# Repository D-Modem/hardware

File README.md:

# pico-serial

Open RP2040 boards for the D-Modem suite: serial adapters and phone-line
USB sticks.

pico-serial connects a phone or computer to vintage serial ports and to
real telephone lines. The phone or computer runs [D-Modem](https://github.com/D-Modem/D-Modem)
or [the D-Modem app](https://github.com/D-Modem/app). Each board has a bare
RP2040 with its own flash, crystal and regulator. The boards do not use a
Pico module.

| Board | What it is | Spec |
| --- | --- | --- |
| pico-serial | USB-C to DB25 RS-232. One female DB25 operates as a modem (DCE) or as a computer port (DTE). The board finds the mode automatically | [SPEC.md](SPEC.md) |
| pico-serial W | The same adapter with Bluetooth: BLE for iPhone and iPad, and classic Bluetooth serial for Android | [SPEC-W.md](SPEC-W.md) |
| pico-serial Line | A USB modem stick for a real telephone line, with a Si3056 DAA. The modem is D-Modem on the host | [SPEC-L.md](SPEC-L.md) |
| pico-serial WB | A wideband stick for bare copper pairs. It samples at 96 kHz for the V.wb mode of D-Modem | [SPEC-WB.md](SPEC-WB.md) |

Status: the specs are drafts. CI builds the firmware and runs its tests
on the host and in an RP2040 emulator. A script makes the board files for
KiCad 9. At this time, nothing has run on a real board.

## Quick start

```sh
cmake -S firmware -B firmware/build -G Ninja   # -DPS_BOARD=hood, w, line, wb or pico
ninja -C firmware/build                        # -> firmware/build/pico-serial-hood.uf2
```

The script `hardware/netlist/build_netlist.py` makes the board files.

## Documentation

The documentation is also a website, [d-modem.github.io/hardware](https://d-modem.github.io/hardware/). The website has reference pages that a script makes from the code.

- [docs/](docs/README.md): an index of all specs and guides
- [Firmware](firmware/README.md): how to build and flash, Bluetooth, tests
- [Control protocol](firmware/PROTOCOL.md): the USB vendor interface for host apps
- [Hardware](hardware/README.md): netlist, schematic, PCB, enclosures

## The D-Modem suite

| Repository | What it is |
| --- | --- |
| [D-Modem](https://github.com/D-Modem/D-Modem) | The open V.92 softmodem: dmodemd, libdmodem and the Asterisk, FreeSWITCH and ARI modules |
| [app](https://github.com/D-Modem/app) | The D-Modem app for Android and iOS: a dial-up modem on a SIP call |
| [hardware](https://github.com/D-Modem/hardware) | pico-serial: RP2040 serial adapters and phone-line USB sticks |
| [menu](https://github.com/D-Modem/menu) | modemmenu: the login and the menu that dial-up callers get to |
| [bbs](https://github.com/D-Modem/bbs) | A bulletin board for telnet, SSH, TN3270 and modem callers |
| [go3270](https://github.com/D-Modem/go3270) | A Go library for 3270 terminal servers, used by bbs |
| [brand](https://github.com/D-Modem/brand) | Logos, colours, type and the naming guide |

ISDN S0 stick (an ISDN basic rate S/T port for D-Modem, TE or NT): see [SPEC-S0.md](SPEC-S0.md).

FPGA line board (a study: ADSL, ISDN U or S0 through gateware and host software): see [SPEC-FX.md](SPEC-FX.md).

## Licence

Firmware: AGPL-3.0-only, or a commercial licence from the D-Modem Authors. Hardware: CERN-OHL-S-2.0, or a commercial licence from the D-Modem Authors. See [LICENSING.md](LICENSING.md). Contributions come with a contributor agreement ([CONTRIBUTING.md](CONTRIBUTING.md)).

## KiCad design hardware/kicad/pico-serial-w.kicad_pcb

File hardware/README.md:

<!-- SPDX-License-Identifier: CERN-OHL-S-2.0 -->
<!-- Copyright (C) 2026 D-Modem Authors -->
# pico-serial hardware

`netlist/build_netlist.py` defines all parts and all connections on the
board. The scripts make the netlist, the readable net list, the JLC parts
list, the schematic and the PCB from it. Thus, change the script, not the
outputs.

The script makes these boards:
- The **hood board** (the default). It fits in a standard DB25 hood.
- **pico-serial W** (`--variant w`, [SPEC-W.md](../SPEC-W.md)). It adds an
  RM2 Bluetooth module, and it is in a 3D-printed hood (`enclosure/`). Its
  files have a `-w` suffix. See [pico-serial W](#pico-serial-w-bluetooth).
- **pico-serial Line** (`--variant line`, [SPEC-L.md](../SPEC-L.md)). It is
  a different device on the same RP2040 core: a USB-C stick that connects to
  a telephone line, for D-Modem. Its files have a `-line` suffix. See
  [pico-serial Line](#pico-serial-line-phone-line-stick).

All files are for **KiCad 9**: KiCad 9 file formats and the KiCad 9.0
symbol and footprint libraries. KiCad 10 also opens them.

| File | What it is |
|---|---|
| `netlist/build_netlist.py` | The circuit: parts, nets, the checks |
| `netlist/pico-serial.net` | KiCad netlist (generated) |
| `netlist/NETLIST.md` | All nets and all parts, in a readable form (generated) |
| `netlist/bom-jlc.csv` | JLC assembly parts list with LCSC numbers (generated) |
| `kicad/build_schematic.py` | Draws the schematic from the netlist script |
| `kicad/pico-serial.kicad_sch` | KiCad schematic, one A2 sheet (generated) |
| `kicad/pico-serial.kicad_sym` | SP3238E and MAX3243E symbols. KiCad does not supply these symbols (generated) |
| `kicad/preview.svg` | Approximate drawing of the sheet for a quick examination (generated) |
| `kicad/build_pcb.py` | Makes the layout of the PCB and routes it: outline, rules, placement, planes |
| `kicad/pico-serial.kicad_pcb` | KiCad PCB, 4 layers (generated) |
| `kicad/pico-serial.kicad_dru` | Two DRC rules for this board (the DB25 cups and the USB-C shell at the edges) |
| `kicad/fab/` | Gerbers + drill (zip) and the JLC placement file (generated) |
| `kicad/render-top.png`, `render-bottom.png` | KiCad 3D renders, without part models (generated) |
| `netlist/pico-serial-w.net`, `NETLIST-w.md`, `bom-jlc-w.csv` | The same for pico-serial W (generated) |
| `kicad/pico-serial-w.*`, `preview-w.svg`, `render-w-*.png` | The schematic, PCB, rules and renders of pico-serial W |
| `kicad/lib/make_footprints.py` | Writes `lib/pico-serial.pretty/`: the RM2 (from the drawing in its datasheet), the M2 screw hole, the RJ11 and the telecom fuse |
| `netlist/*-line.*`, `kicad/pico-serial-line.*`, `kicad/render-line-*.png` | The netlist, BOM, schematic, PCB, rules and renders of pico-serial Line |
| `netlist/*-wb.*`, `kicad/pico-serial-wb.*`, `kicad/render-wb-*.png` | The netlist, BOM, schematic, PCB, rules and renders of pico-serial WB |
| `enclosure/stick.py`, `enclosure/out-line/` | The printed shell of the Line stick, its board outline and placement |
| `kicad/fp-lib-table` | Points KiCad to `lib/pico-serial.pretty` |

## Regenerate

```sh
python3 hardware/netlist/build_netlist.py       # checks + netlist, NETLIST.md, BOM
python3 hardware/kicad/build_schematic.py   # checks + schematic and preview
python3 hardware/kicad/build_pcb.py --kicad-fp kicad-footprints --route --fab   # PCB (see below)
```

For pico-serial W, add `--variant w` to each command.

The netlist and schematic scripts do not need KiCad or a network
connection. The schematic script uses the symbols in the cache
`kicad/lib/symbol-cache.sexp`.

To compare all pins with the libraries of KiCad, and to update the symbol
cache, give the scripts the checkouts of the KiCad 9.0 libraries:

```sh
git clone --depth 1 --branch 9.0.6 https://gitlab.com/kicad/libraries/kicad-symbols.git
git clone --depth 1 --branch 9.0.6 https://gitlab.com/kicad/libraries/kicad-footprints.git
python3 hardware/netlist/build_netlist.py --kicad-sym kicad-symbols --kicad-fp kicad-footprints
python3 hardware/kicad/build_schematic.py --kicad-sym9 kicad-symbols
```

The script stops with an error, and writes nothing, if one of these
conditions occurs:
- A pin is not connected and it is not in the list of pins that are open
  intentionally.
- A net has only one pin.
- A net has two outputs.
- An RS-232 line does not have exactly one driver and one receiver.
- A power input is not on a supply net.
- With the KiCad checkouts: a pin number or name is different from the
  symbol of KiCad, or a footprint does not have a pad for a pin.

## What's in it

The circuit follows `../SPEC.md` (draft 0.3): §4.2–4.8 for the parts and
§4.6 for the GPIO map.

- **Power and USB:**
  - USB-C (HRO TYPE-C-31-M-12) with a separate 5.1 kΩ on each CC pin.
  - 0.5 A PTC fuse, 5 V TVS diode, USBLC6 ESD protection.
  - AP2112K 3.3 V regulator, VBUS ÷2 sense into GP29.
- **RP2040:**
  - The minimal design of Raspberry Pi: decoupling on each pin, 12 MHz
    crystal with 15 pF capacitors and 1 kΩ on XOUT, 27 Ω USB series
    resistors.
  - W25Q128JV flash.
  - BOOTSEL and RESET buttons, 10 kΩ RUN pull-up.
- **RS-232:**
  - SP3238E (chip A, DCE) and MAX3243E (chip B, DTE) on the same 8 DB25
    pins. Thus each line has one driver and one receiver.
  - Each chip has 220 nF + 1 µF charge-pump capacitors and 1 µF + 100 nF
    on VCC.
  - 100 kΩ pull-downs keep the two chips off until the firmware selects a
    role.
- **DB25:** solder-cup female (MH Connectors MHDB25SS). Pin 7 to GND, pin
  1 to GND through a 0 Ω link. All other unused pins stay open.
- **Optional:** six status LEDs on GP22–27, not installed (DNP).
- **Test pads:** VBUS, 3V3, 1V1, GND, SWCLK, SWDIO, RUN, GP28, and the TX/RX
  lines of the two chips.

The two RS-232 chips have no KiCad symbol. We copied their pin tables from
the datasheets (MaxLinear SP3238E rev 1.0.1; TI MAX3243E SLLS657E,
Table 6-2). The script identifies these tables as copies. The pins of all
other parts match the library symbols of KiCad.

## The schematic

`kicad/pico-serial.kicad_sch` is one A2 sheet, with these blocks:
- USB-C, protection and supply.
- RP2040 and its decoupling.
- Crystal, flash and buttons.
- Chip A (DCE) and chip B (DTE), each with its charge-pump capacitors.
- The DB25.
- The optional LEDs.
- Test pads and the power flags that ERC needs.

Each pin ends in a short wire with a net label or a power symbol. Thus
parts connect by name, not by long wires. Each part has its LCSC number, a
note about its function, and its footprint.

The schematic script stops and does not write the file if one of these
conditions occurs:
- The connections that it reads back from the drawing are different from
  the netlist (a missing pin, an extra connection, a pin that touches the
  middle of a wire).
- Two texts, labels or symbols overlap.

A script makes the schematic. Thus the next run overwrites changes that you
make by hand. Change `build_netlist.py` and regenerate. Alternatively, stop
the use of the script and, after that, edit the schematic in KiCad.

## The PCB

`kicad/build_pcb.py` makes `kicad/pico-serial.kicad_pcb` with the Python
module of KiCad 9 (pcbnew). **Status:** fully routed. The DRC of KiCad
9.0.9 finds no errors, no warnings and no unconnected items. The PCB
matches the schematic exactly (the schematic parity check of DRC). CI does
all of these checks on each change (`.github/workflows/hardware.yml`). No
person has done a review at this time, and nobody has built a board.

- **Board:** about 37 × 38 mm, 4 layers, 1.6 mm. It uses the standard
  4-layer process of JLCPCB with margin (0.127 mm clearance, 0.15 mm
  tracks, 0.25 mm via drills). The outline is the inferred outline of SPEC §7.2: full width at the DB25,
  narrower behind, and a tongue for the USB-C into the cable exit of the
  hood. The values are at the top of the script. **Confirm the outline on
  a sample hood**.
- **DB25:** the front edge of the board goes between the solder cups: pins
  1-13 on the top, 14-25 on the bottom.
- **Top:** RP2040, flash, crystal, buttons. The USB-C, ESD, fuse, TVS and
  the regulator are at the back.
- **Bottom:**
  - The two transceivers with their charge pumps, immediately behind the
    cups. (From the top, chip A/U5 is on the left and chip B/U6 is on the
    right. This sequence has the fewest crossing connections.)
  - The decoupling of the RP2040, about 2 mm from its pins.
  - Test pads.
  - The optional LEDs.
- **Layers:**
  - F.Cu: signals, then a GND pour.
  - In1.Cu: solid GND plane below all parts.
  - In2.Cu: signals, then a +3V3 pour in the remaining space.
  - B.Cu: signals, then a GND pour.
- **Vias:** before the routing, each GND and +3V3 pad gets its own short
  stub and via. The +3V3 pins of the RP2040 have their vias below the
  package, between the pins and the exposed pad. Thus the ring around the
  package stays free for the signals. The exposed pad has four vias.
- **Kept clear:**
  - The USB D+/D- path from the RP2040 to the series resistors and the
    ESD chip has no vias across it.
  - No track goes below the crystal on the top layer (keep-outs between
    its pads). The In1 GND plane shields the crystal from the remaining
    circuit.
  - A 0.35 mm band inside the board edge has no tracks or vias.
    (Freerouting does not apply the edge clearance of KiCad.)
- **Silkscreen:** on the top, the name and revision, "DCE / DTE auto", the
  gender-changer note and `CERN-OHL-S-2.0`. On the bottom, between the cups
  and the chips, `github.com/D-Modem/hardware` (the Source Location of the
  licence). The reference designators are on the fab layers, because there
  is no space for them on the silkscreen.
- **Linked to the schematic:** each footprint has the ID of its symbol, and
  each pad has its net, with the name that KiCad gives it.

### Test pads (bottom)

1 mm pads on a 2.6 mm grid behind the flash, for pogo pins. GP28 is
separate, adjacent to the left side of the RP2040. Coordinates are in mm,
from the middle of the DB25 edge, toward the USB-C:

| y \ x | 6.5 | 9.1 | 11.7 | 14.3 |
|---|---|---|---|---|
| 21.0 | TP1 VBUS | TP2 3V3 | TP3 1V1 | TP4 GND |
| 23.6 | TP5 SWCLK | TP6 SWDIO | TP7 RUN | TP9 A_TX |
| 26.2 | TP10 A_RX | TP11 B_TX | TP12 B_RX | |

TP8 (GP28) is at x = -9.5, y = 23.8.

### Rebuilding it

```sh
python3 hardware/kicad/build_pcb.py --kicad-fp kicad-footprints \
    --route --freerouting freerouting-1.9.0.jar --fab
```

- **Necessary items:** KiCad 9 (its Python module and `kicad-cli`), the
  KiCad 9.0 footprint libraries, Java, `xvfb-run`, and
  [Freerouting](https://github.com/freerouting/freerouting) 1.9.0.
  Freerouting 2.1 ignores its pass limit on the command line. Thus use
  version 1.9. It needs a display, thus `xvfb-run` is necessary.
- **Routing:** Freerouting routes all nets except GND. The plane and the
  vias already connect GND. Freerouting runs in rounds, and each round
  starts from the last round (`--rounds`). Then a small grid router in the
  script (A* on a 0.1 mm grid on the three signal layers, compared with
  the copper shapes of KiCad) connects the items that are still
  unconnected.
- **Repeatable:** Freerouting gives the same result for the same board and
  pass count. If a pass count does not route all nets, the script tries
  the next value in `--passes` (40, 30, 50, 35, 45). It keeps the first
  value that routes all nets. It shows the value that it kept. If no value
  routes all nets, it gives a warning.
- **Without `--route`**, the script writes the placed board without routes
  (with its vias and planes). `--ses` imports a saved Freerouting session
  in place of the routing.
- **`--fab`** writes `fab/pico-serial-gerbers.zip` and
  `fab/pico-serial-cpl-jlc.csv`. Upload the zip, `netlist/bom-jlc.csv` and
  the CPL file to JLCPCB. The DB25 is hand-soldered, thus it is not in the
  two lists.
- **Before you order assembly:** parts go on the two sides (two-sided
  assembly costs more). Examine the rotation of each part in the preview
  of JLC, specially the parts on the bottom side. The CPL comes directly
  from KiCad, and the footprints of JLC do not always agree on 0°.

## Using it in KiCad

1. Open `kicad/pico-serial.kicad_pro` in KiCad 9 or 10. The project
   table points to `pico-serial.kicad_sym`, which has the two RS-232
   symbols. The schematic also contains all symbols.
2. Do the ERC. The result is clean (KiCad 9.0.9, with the 9.0 libraries).
3. Open the PCB and do the DRC, with the schematic parity check. The
   result is clean.
4. The PCB is linked to the schematic. Thus **Update PCB from Schematic**
   operates as usual. The parity check of DRC does the same comparison,
   and it finds no difference. (Nobody has used the update function,
   because there was no KiCad GUI where we made these files.)

## Before ordering

- **Get a review of the layout from a person.** A router made the layout.
  Thus, examine the items that a router does not consider: the crystal and
  its loop, the decoupling, the USB pair, the RS-232 lines near the cups.
  The routes are complete, but they are not necessarily good.
- Make the board outline final from the sample connector and hood (SPEC
  §7, §9). Make sure that the board goes between the cups of the DB25.
- Do a bench test of the leakage of the SP3238E in shutdown (SPEC §8). If
  it fails, change the DCE chip to the TI TRS3238E (TSSOP-28). Then its
  footprint also changes.

## pico-serial W (Bluetooth)

This is the same circuit and a Raspberry Pi RM2 radio module, on a larger
board for the 3D-printed hood ([SPEC-W.md](../SPEC-W.md), `enclosure/`).
All scripts accept `--variant w`. Its files are `pico-serial-w.*`.

```sh
python3 hardware/netlist/build_netlist.py --variant w
python3 hardware/kicad/build_schematic.py --variant w
python3 hardware/kicad/build_pcb.py --variant w --kicad-fp kicad-footprints \
    --route --freerouting freerouting-1.9.0.jar --fab
```

**Status:** fully routed. DRC finds no errors and no unconnected items,
and the PCB matches its schematic. ERC is clean. CI does the checks on the
two boards. No person has done a review, and nobody has built a board.

- **Circuit changes** (SPEC-W §3):
  - The RM2 on GP23-25 and GP29, wired as on Pico W (470 Ω and 10 kΩ into
    the shared GP24).
  - 10 µF + 100 nF + 22 µF at its supply.
  - Five LEDs, installed (BT, TR, CD on RP2040 pins; RD and SD on the own
    GPIOs of the RM2).
  - VBUS sense on GPIO0 of the RM2.
  - A pairing button on GP28 (thus there is no GP28 test pad).
- **Outline and fixed positions** come from `enclosure/w_hood.py`, not
  from this script: the outline, three M2 screw holes, the RM2 (antenna
  end flush with the back edge of the board), the USB-C in its tongue, the
  LEDs below the light tubes of the hood and the button below its pinhole.
  Change them in `enclosure/w_hood.py`. Then the hood and the board stay
  the same.
- **Front half:** the DB25, the two RS-232 chips, the RP2040, flash,
  crystal and buttons have the same positions as on the hood board. The
  front strip is 0.5 mm narrower (thumbscrew pockets). Thus chip A and its
  charge pumps are 0.6 mm more to the inside.
- **Antenna keep-out:** a rule area with no copper on any layer (tracks,
  vias, pads, pours, planes). It covers the strip of the board that is in
  the 35.5 × 18.5 mm keep-out of the RM2. The remaining part of the
  keep-out is air in the hood.
- **Screw holes:** 2.3 mm, unplated. An area of 5.4 mm has no copper and
  no parts (for the screw head and the bosses of the hood). They are
  footprints only on the board (`lib/pico-serial.pretty/MountingHole_M2`),
  not in the schematic.
- **RM2 footprint:** `lib/make_footprints.py`, from Figure 6 of the
  datasheet: 21 pads, 1.5 mm pitch, which extend 0.5 mm beyond the module.
  Compare it with a real module before you order.
- **Assembly:** LCSC does not have the RM2 in stock. Thus the script marks
  it as installed by hand, and it is not in the BOM or in the CPL. Solder
  it by hand, or send it to JLC as a consigned part. The DB25 is
  hand-soldered, as on the hood board.
- **Before ordering:** do all items in "Before ordering" above. Also do a
  test print of the hood, to confirm the screw holes and the positions of
  the LEDs and the button.

## pico-serial Line (phone-line stick)

This is a USB-C stick for a telephone line, with the shape of the USB Modem
of Apple ([SPEC-L.md](../SPEC-L.md)). It has the RP2040 core and a
Skyworks Si3056 + Si3018 DAA. The modem itself is D-Modem on the computer
or phone (`dmodemd --usb`). All scripts accept `--variant line`. The shell
is `enclosure/stick.py`.

```sh
python3 hardware/netlist/build_netlist.py --variant line
python3 hardware/kicad/build_schematic.py --variant line
python3 hardware/enclosure/stick.py          # the shell; needs CadQuery
python3 hardware/kicad/build_pcb.py --variant line --kicad-fp kicad-footprints \
    --route --freerouting freerouting-1.9.0.jar --fab
```

**Status:** fully routed (190 vias, 1036 tracks). The DRC of KiCad finds
no errors and no unconnected items, and the PCB matches its schematic. ERC
is clean. No person has done a review, and nobody has built a board.

> **WARNING: BEFORE YOU CONNECT THE LINE STICK TO A PHONE LINE, GET AN
> EXAMINATION OF THE LINE SIDE AND THE ISOLATION GAP FROM A PERSON WHO
> KNOWS TELECOM SAFETY.** No person has done a review of this layout.

- **Board:** 78.4 × 20.6 mm, 4 layers, on the outline that `stick.py`
  sets. The RJ11 is at the front edge, and its opening is flush with the
  end of the stick. The USB-C is at the back.
- **Line side** (front, about 30 mm): the surge suppressor, the 1.25 A
  telecom fuse, the bridge, the Si3018 and its hook switch, the DC
  termination and the caller-ID parts, on the two sides of the board.
  **No ground plane or pour** (Skyworks AN67): the planes and pours stop
  at the isolation gap.
- **Isolation gap:** a 2.5 mm band across the board, on all layers, with no
  tracks, vias or pours. Only the four Y2 capacitors go across it (C1, C2:
  the data path; C8, C9: TIP and RING to ground). A DRC rule
  (`pico-serial-line.kicad_dru`) also keeps 2.5 mm between all line-side
  copper and all USB-side copper.
- **Net classes:** `TipRing` (TIP, RING, the + of the bridge: the ring
  signal and the loop current): 0.3 mm tracks, 0.4 mm clearance. `Line`
  (the low-voltage side of the Si3018): 0.25 mm.
- **USB side:** the Si3056 adjacent to the gap, the one screw, the two LEDs
  below the light tubes of the shell, the RP2040 with its flash on the
  bottom, then the USB-C with its ESD, fuse and regulator.
- **Installed by hand or consigned:** the Si3056 and Si3018 (DigiKey; the
  Si3056 is "not for new designs") and the through-hole RJ11. They are not
  in the JLC BOM or in the CPL.
- **Not examined at this time:** the body of the RJ11 against a real RJ11
  (its drawing gives the pins and pegs; we got the edges of the body from
  the drawing), and the fit of the shell (not printed).

## pico-serial WB (wideband bare-pair stick)

This is the sibling of the Line stick for bare copper pairs
([SPEC-WB.md](../SPEC-WB.md)). It has the same RP2040 core and USB end, a
TI TLV320AIC3204 codec that samples at 96 kHz, and a Pulse PE-65848 line
transformer. Two WB sticks communicate with each other through the pair.
The modem is the wideband mode of D-Modem on the computer or phone. All
scripts accept `--variant wb`. The shell is the shell of the Line stick
(`enclosure/stick.py --variant wb`).

```sh
python3 hardware/netlist/build_netlist.py --variant wb
python3 hardware/kicad/build_schematic.py --variant wb
python3 hardware/enclosure/stick.py --variant wb     # the shell; needs CadQuery
python3 hardware/kicad/build_pcb.py --variant wb --kicad-fp kicad-footprints \
    --route --freerouting freerouting-1.9.0.jar --fab
```

**Status:** fully routed. The DRC of KiCad finds no errors and no unconnected items, and the PCB matches its schematic. ERC is clean. The fab files are in `kicad/fab/`. No person has done a review, and nobody has built a board.

- **Board:** the outline and USB end of the Line stick (RP2040, flash,
  USB-C, regulator). The screw is 6.4 mm from the centre line. The two LEDs
  (LINK and DATA) are 3 mm more to the front than on the Line stick. Thus
  the connections of the codec can go down the middle.
  `stick.py --variant wb` moves the boss and the light tubes of the shell
  to match.
- **Pair side** (front): the RJ11, the 1.25 A telecom fuse and the sidactor
  on the bottom, ferrites adjacent to the transformer, and the DC block
  (two 1 µF 250 V in series, 0.5 µF / 500 V) in the split line winding of
  the transformer. **No ground plane or pour.**
- **Isolation gap:** a 4 mm band across the board below the transformer,
  on all layers, with no tracks, vias or pours. Only the transformer goes
  across it: the pads of its codec winding and of its line winding are
  10 mm apart. A DRC rule (`pico-serial-wb.kicad_dru`) also keeps 2.5 mm
  between all pair-side (`TipRing`) copper and all USB-side copper.
- **Codec side:**
  - The hybrid on the bottom behind the transformer (60.4 Ω drive
    resistors, the ×10 replica arm, the 1 kΩ + 1 µF into each mixer
    input).
  - The clamps (a 5 V TVS across the winding, a BAV99 on each end).
  - The codec on the top, with its supply and reference capacitors.
- **Installed by hand:** the through-hole RJ11. The transformer is a JLC
  part (C7261159), but the stock is low (about 250).
- **Not examined at this time:** the bandwidth and saturation of the
  transformer (its datasheet gives neither: sweep one from 1 to 200 kHz),
  the hybrid values on a real cable, and the fit of the shell (not
  printed). The 1812 DC block capacitors are on the bottom, below the
  2.2 mm clearance of the shell.

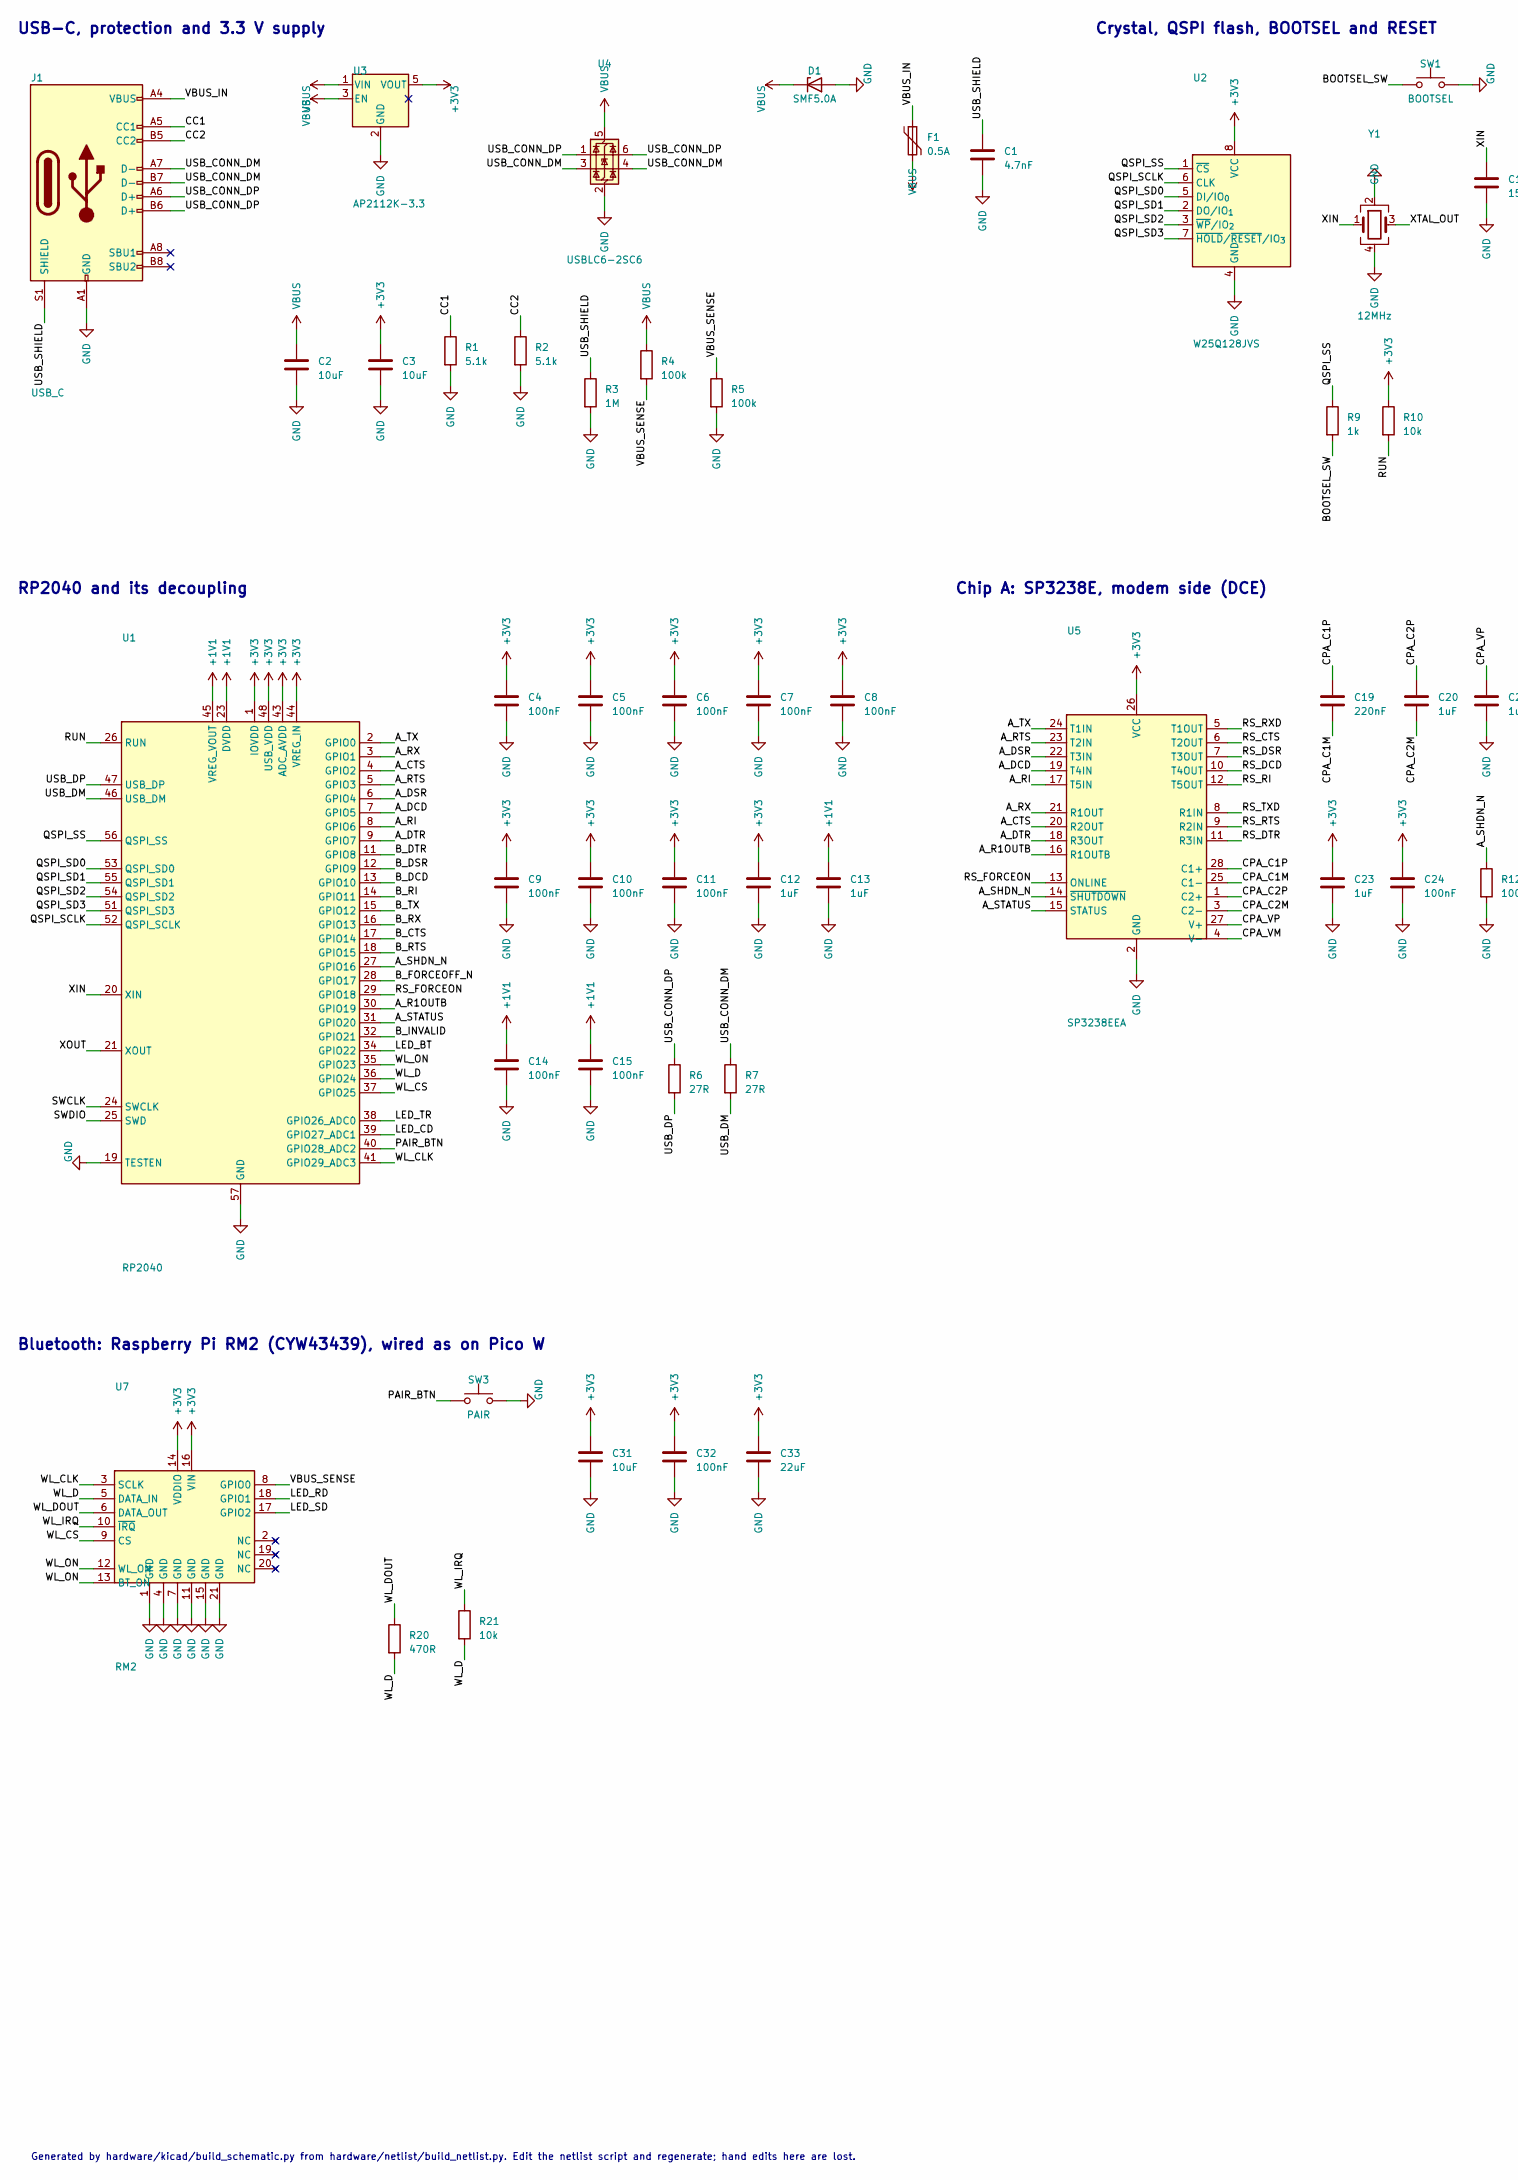
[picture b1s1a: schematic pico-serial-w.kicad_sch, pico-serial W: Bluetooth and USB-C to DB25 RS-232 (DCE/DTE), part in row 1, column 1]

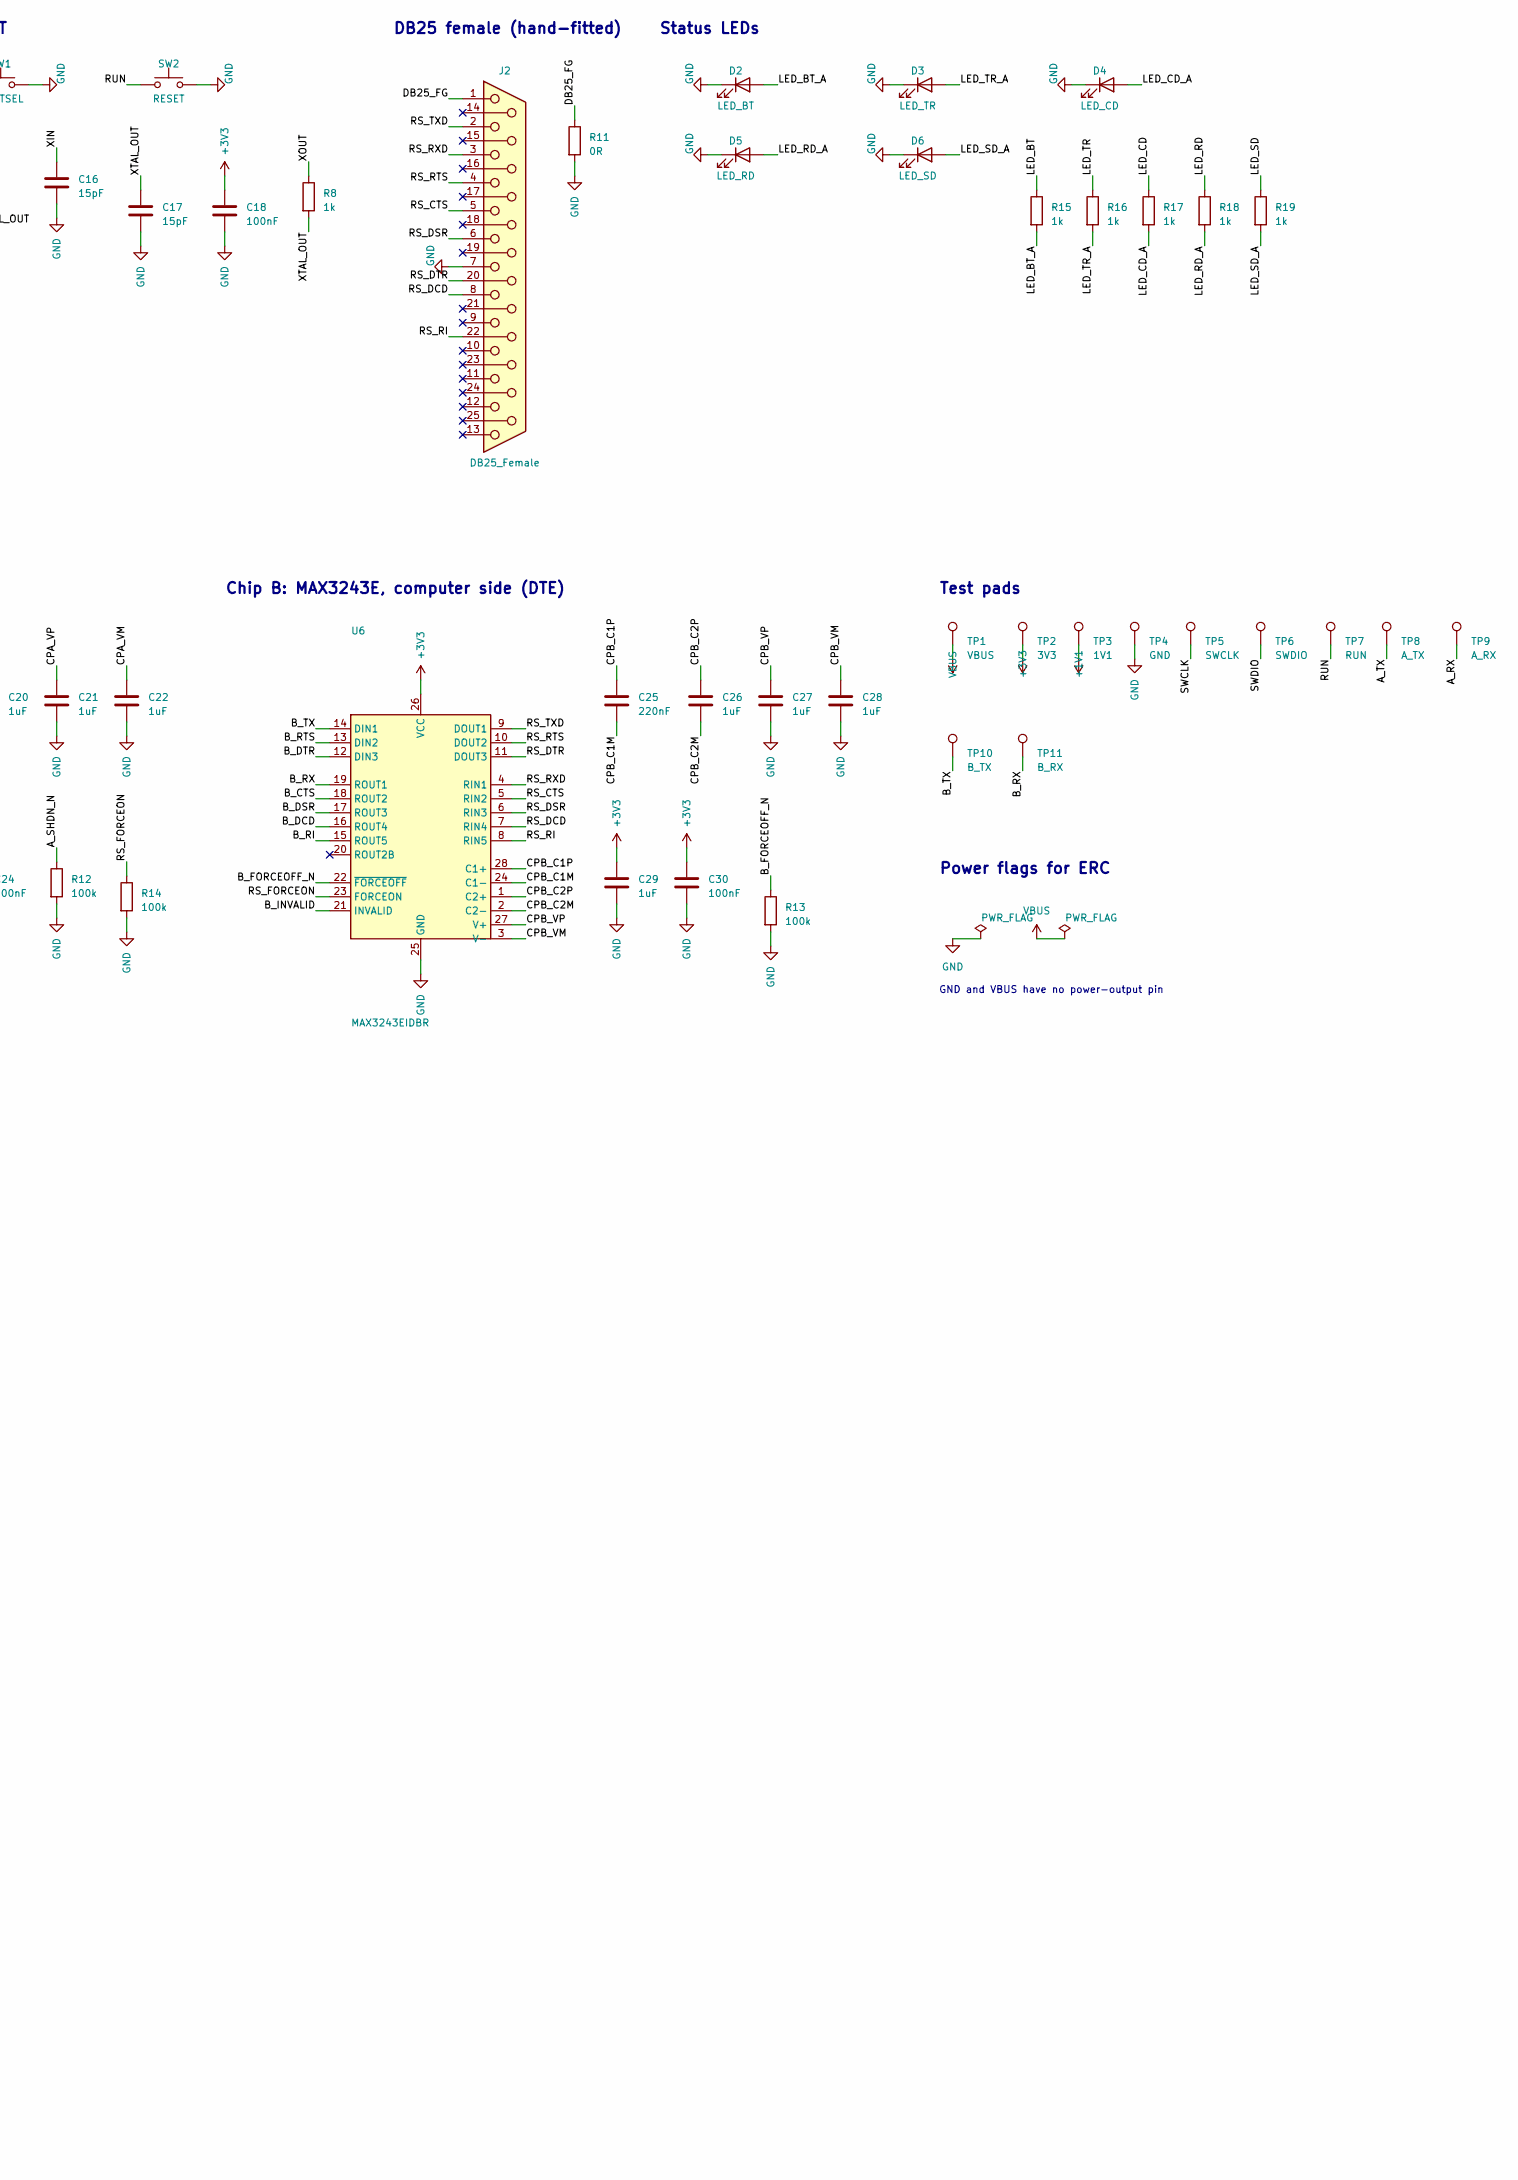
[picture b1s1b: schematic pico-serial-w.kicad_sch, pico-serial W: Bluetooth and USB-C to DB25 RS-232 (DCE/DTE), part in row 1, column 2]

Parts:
C1: 4.7nF; C_0402_1005Metric; LCSC C1538
C2, C3, C31: 10uF; C_0603_1608Metric; LCSC C19702
C4, C5, C6, C7, C8, C9, C10, C11, C14, C15, C18, C24, C30, C32: 100nF; C_0402_1005Metric; LCSC C1525
C12, C13, C23, C29: 1uF; C_0402_1005Metric; LCSC C52923
C16, C17: 15pF; C_0402_1005Metric; LCSC C1548
C19, C25: 220nF; C_0402_1005Metric; LCSC C16772
C20, C21, C22, C26, C27, C28: 1uF; C_0603_1608Metric; LCSC C15849
C33: 22uF; C_0805_2012Metric; LCSC C45783
D1: SMF5.0A; D_SOD-123F; LCSC C151296
D2: LED_BT; LED_0603_1608Metric; LCSC C2286
D3: LED_TR; LED_0603_1608Metric; LCSC C2286
D4: LED_CD; LED_0603_1608Metric; LCSC C2286
D5: LED_RD; LED_0603_1608Metric; LCSC C2286
D6: LED_SD; LED_0603_1608Metric; LCSC C2286
F1: 0.5A; Fuse_1206_3216Metric; LCSC C163512
J1: USB_C; USB_C_Receptacle_HRO_TYPE-C-31-M-12; LCSC C165948
J2: DB25_Female; DSUB-25_Socket_EdgeMount_P2.77mm; LCSC C19601171
R1, R2: 5.1k; R_0402_1005Metric; LCSC C25905
R3: 1M; R_0402_1005Metric; LCSC C26083
R4, R5, R12, R13, R14: 100k; R_0402_1005Metric; LCSC C25741
R6, R7: 27R; R_0402_1005Metric; LCSC C25100
R8, R9, R15, R16, R17, R18, R19: 1k; R_0402_1005Metric; LCSC C11702
R10, R21: 10k; R_0402_1005Metric; LCSC C25744
R11: 0R; R_0402_1005Metric; LCSC C17168
R20: 470R; R_0402_1005Metric; LCSC C25117
SW1: BOOTSEL; SW_SPST_TS-1088-xR020; LCSC C720477
SW2: RESET; SW_SPST_TS-1088-xR020; LCSC C720477
SW3: PAIR; SW_SPST_TS-1088-xR020; LCSC C720477
TP1: VBUS; TestPoint_Pad_D1.0mm
TP2: 3V3; TestPoint_Pad_D1.0mm
TP3: 1V1; TestPoint_Pad_D1.0mm
TP4: GND; TestPoint_Pad_D1.0mm
TP5: SWCLK; TestPoint_Pad_D1.0mm
TP6: SWDIO; TestPoint_Pad_D1.0mm
TP7: RUN; TestPoint_Pad_D1.0mm
TP8: A_TX; TestPoint_Pad_D1.0mm
TP9: A_RX; TestPoint_Pad_D1.0mm
TP10: B_TX; TestPoint_Pad_D1.0mm
TP11: B_RX; TestPoint_Pad_D1.0mm
U1: RP2040; QFN-56-1EP_7x7mm_P0.4mm_EP3.2x3.2mm; LCSC C2040
U2: W25Q128JVS; SOIC-8_5.3x5.3mm_P1.27mm; LCSC C97521
U3: AP2112K-3.3; SOT-23-5; LCSC C51118
U4: USBLC6-2SC6; SOT-23-6; LCSC C7519
U5: SP3238EEA; SSOP-28_5.3x10.2mm_P0.65mm; LCSC C49669
U6: MAX3243EIDBR; SSOP-28_5.3x10.2mm_P0.65mm; LCSC C353887
U7: RM2; RaspberryPi_RM2
Y1: 12MHz; Crystal_SMD_3225-4Pin_3.2x2.5mm; LCSC C20625731

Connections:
+1V1: C13.1, C14.1, C15.1, TP3.1, U1.23 (DVDD), U1.45 (VREG_VOUT), U1.50 (DVDD)
+3V3: C3.1, C4.1, C5.1, C6.1, C7.1, C8.1, C9.1, C10.1, C11.1, C12.1, C18.1, C23.1, C24.1, C29.1, C30.1, C31.1, C32.1, C33.1, R10.1, TP2.1, U1.1 (IOVDD), U1.10 (IOVDD), U1.22 (IOVDD), U1.33 (IOVDD), U1.42 (IOVDD), U1.43 (ADC_AVDD), U1.44 (VREG_IN), U1.48 (USB_VDD), U1.49 (IOVDD), U2.8 (VCC), U3.5 (VOUT), U5.26 (VCC), U6.26 (VCC), U7.14 (VDDIO), U7.16 (VIN)
/A_CTS: U1.4 (GPIO2), U5.20 (R2OUT)
/A_DCD: U1.7 (GPIO5), U5.19 (T4IN)
/A_DSR: U1.6 (GPIO4), U5.22 (T3IN)
/A_DTR: U1.9 (GPIO7), U5.18 (R3OUT)
/A_R1OUTB: U1.30 (GPIO19), U5.16 (R1OUTB)
/A_RI: U1.8 (GPIO6), U5.17 (T5IN)
/A_RTS: U1.5 (GPIO3), U5.23 (T2IN)
/A_RX: TP9.1, U1.3 (GPIO1), U5.21 (R1OUT)
/A_SHDN_N: R12.1, U1.27 (GPIO16), U5.14 (~SHUTDOWN)
/A_STATUS: U1.31 (GPIO20), U5.15 (STATUS)
/A_TX: TP8.1, U1.2 (GPIO0), U5.24 (T1IN)
/BOOTSEL_SW: R9.2, SW1.1
/B_CTS: U1.17 (GPIO14), U6.18 (ROUT2)
/B_DCD: U1.13 (GPIO10), U6.16 (ROUT4)
/B_DSR: U1.12 (GPIO9), U6.17 (ROUT3)
/B_DTR: U1.11 (GPIO8), U6.12 (DIN3)
/B_FORCEOFF_N: R13.1, U1.28 (GPIO17), U6.22 (~FORCEOFF)
/B_INVALID: U1.32 (GPIO21), U6.21 (INVALID)
/B_RI: U1.14 (GPIO11), U6.15 (ROUT5)
/B_RTS: U1.18 (GPIO15), U6.13 (DIN2)
/B_RX: TP11.1, U1.16 (GPIO13), U6.19 (ROUT1)
/B_TX: TP10.1, U1.15 (GPIO12), U6.14 (DIN1)
/CC1: J1.A5 (CC1), R1.1
/CC2: J1.B5 (CC2), R2.1
/CPA_C1M: C19.2, U5.25 (C1-)
/CPA_C1P: C19.1, U5.28 (C1+)
/CPA_C2M: C20.2, U5.3 (C2-)
/CPA_C2P: C20.1, U5.1 (C2+)
/CPA_VM: C22.1, U5.4 (V-)
/CPA_VP: C21.1, U5.27 (V+)
/CPB_C1M: C25.2, U6.24 (C1-)
/CPB_C1P: C25.1, U6.28 (C1+)
/CPB_C2M: C26.2, U6.2 (C2-)
/CPB_C2P: C26.1, U6.1 (C2+)
/CPB_VM: C28.1, U6.3 (V-)
/CPB_VP: C27.1, U6.27 (V+)
/DB25_FG: J2.1, R11.1
/LED_BT: R15.1, U1.34 (GPIO22)
/LED_BT_A: D2.2 (A), R15.2
/LED_CD: R17.1, U1.39 (GPIO27_ADC1)
/LED_CD_A: D4.2 (A), R17.2
/LED_RD: R18.1, U7.18 (GPIO1)
/LED_RD_A: D5.2 (A), R18.2
/LED_SD: R19.1, U7.17 (GPIO2)
/LED_SD_A: D6.2 (A), R19.2
/LED_TR: R16.1, U1.38 (GPIO26_ADC0)
/LED_TR_A: D3.2 (A), R16.2
/PAIR_BTN: SW3.1, U1.40 (GPIO28_ADC2)
/QSPI_SCLK: U1.52 (QSPI_SCLK), U2.6 (CLK)
/QSPI_SD0: U1.53 (QSPI_SD0), U2.5 (DI/IO_{0})
/QSPI_SD1: U1.55 (QSPI_SD1), U2.2 (DO/IO_{1})
/QSPI_SD2: U1.54 (QSPI_SD2), U2.3 (~WP/IO_{2})
/QSPI_SD3: U1.51 (QSPI_SD3), U2.7 (~HOLD/~RESET/IO_{3})
/QSPI_SS: R9.1, U1.56 (QSPI_SS), U2.1 (~CS)
/RS_CTS: J2.5, U5.6 (T2OUT), U6.5 (RIN2)
/RS_DCD: J2.8, U5.10 (T4OUT), U6.7 (RIN4)
/RS_DSR: J2.6, U5.7 (T3OUT), U6.6 (RIN3)
/RS_DTR: J2.20, U5.11 (R3IN), U6.11 (DOUT3)
/RS_FORCEON: R14.1, U1.29 (GPIO18), U5.13 (ONLINE), U6.23 (FORCEON)
/RS_RI: J2.22, U5.12 (T5OUT), U6.8 (RIN5)
/RS_RTS: J2.4, U5.9 (R2IN), U6.10 (DOUT2)
/RS_RXD: J2.3, U5.5 (T1OUT), U6.4 (RIN1)
/RS_TXD: J2.2, U5.8 (R1IN), U6.9 (DOUT1)
/RUN: R10.2, SW2.1, TP7.1, U1.26 (RUN)
/SWCLK: TP5.1, U1.24 (SWCLK)
/SWDIO: TP6.1, U1.25 (SWD)
/USB_CONN_DM: J1.A7 (D-), J1.B7 (D-), R7.1, U4.3 (I/O2), U4.4 (I/O2)
/USB_CONN_DP: J1.A6 (D+), J1.B6 (D+), R6.1, U4.1 (I/O1), U4.6 (I/O1)
/USB_DM: R7.2, U1.46 (USB_DM)
/USB_DP: R6.2, U1.47 (USB_DP)
/USB_SHIELD: C1.1, J1.S1 (SHIELD), R3.1
/VBUS_IN: F1.1, J1.A4 (VBUS), J1.A9 (VBUS), J1.B4 (VBUS), J1.B9 (VBUS)
/VBUS_SENSE: R4.2, R5.1, U7.8 (GPIO0)
/WL_CLK: U1.41 (GPIO29_ADC3), U7.3 (SCLK)
/WL_CS: U1.37 (GPIO25), U7.9 (CS)
/WL_D: R20.2, R21.2, U1.36 (GPIO24), U7.5 (DATA_IN)
/WL_DOUT: R20.1, U7.6 (DATA_OUT)
/WL_IRQ: R21.1, U7.10 (~IRQ)
/WL_ON: U1.35 (GPIO23), U7.12 (WL_ON), U7.13 (BT_ON)
/XIN: C16.1, U1.20 (XIN), Y1.1
/XOUT: R8.1, U1.21 (XOUT)
/XTAL_OUT: C17.1, R8.2, Y1.3
GND: C1.2, C2.2, C3.2, C4.2, C5.2, C6.2, C7.2, C8.2, C9.2, C10.2, C11.2, C12.2, C13.2, C14.2, C15.2, C16.2, C17.2, C18.2, C21.2, C22.2, C23.2, C24.2, C27.2, C28.2, C29.2, C30.2, C31.2, C32.2, C33.2, D1.2 (A), D2.1 (K), D3.1 (K), D4.1 (K), D5.1 (K), D6.1 (K), J1.A1 (GND), J1.A12 (GND), J1.B1 (GND), J1.B12 (GND), J2.7, R1.2, R2.2, R3.2, R5.2, R11.2, R12.2, R13.2, R14.2, SW1.2, SW2.2, SW3.2, TP4.1, U1.19 (TESTEN), U1.57 (GND), U2.4 (GND), U3.2 (GND), U4.2 (GND), U5.2 (GND), U6.25 (GND), U7.1 (GND), U7.4 (GND), U7.7 (GND), U7.11 (GND), U7.15 (GND), U7.21 (GND), Y1.2, Y1.4
VBUS: C2.1, D1.1 (K), F1.2, R4.1, TP1.1, U3.1 (VIN), U3.3 (EN), U4.5 (VBUS)

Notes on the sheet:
GND and VBUS have no power-output pin
USB-C, protection and 3.3 V supply
Crystal, QSPI flash, BOOTSEL and RESET
DB25 female (hand-fitted)
Status LEDs
RP2040 and its decoupling
Chip A: SP3238E, modem side (DCE)
Chip B: MAX3243E, computer side (DTE)
Test pads
Power flags for ERC
Bluetooth: Raspberry Pi RM2 (CYW43439), wired as on Pico W
Generated by hardware/kicad/build_schematic.py from hardware/netlist/build_netlist.py. Edit the netlist script and regenerate; hand edits here are lost.

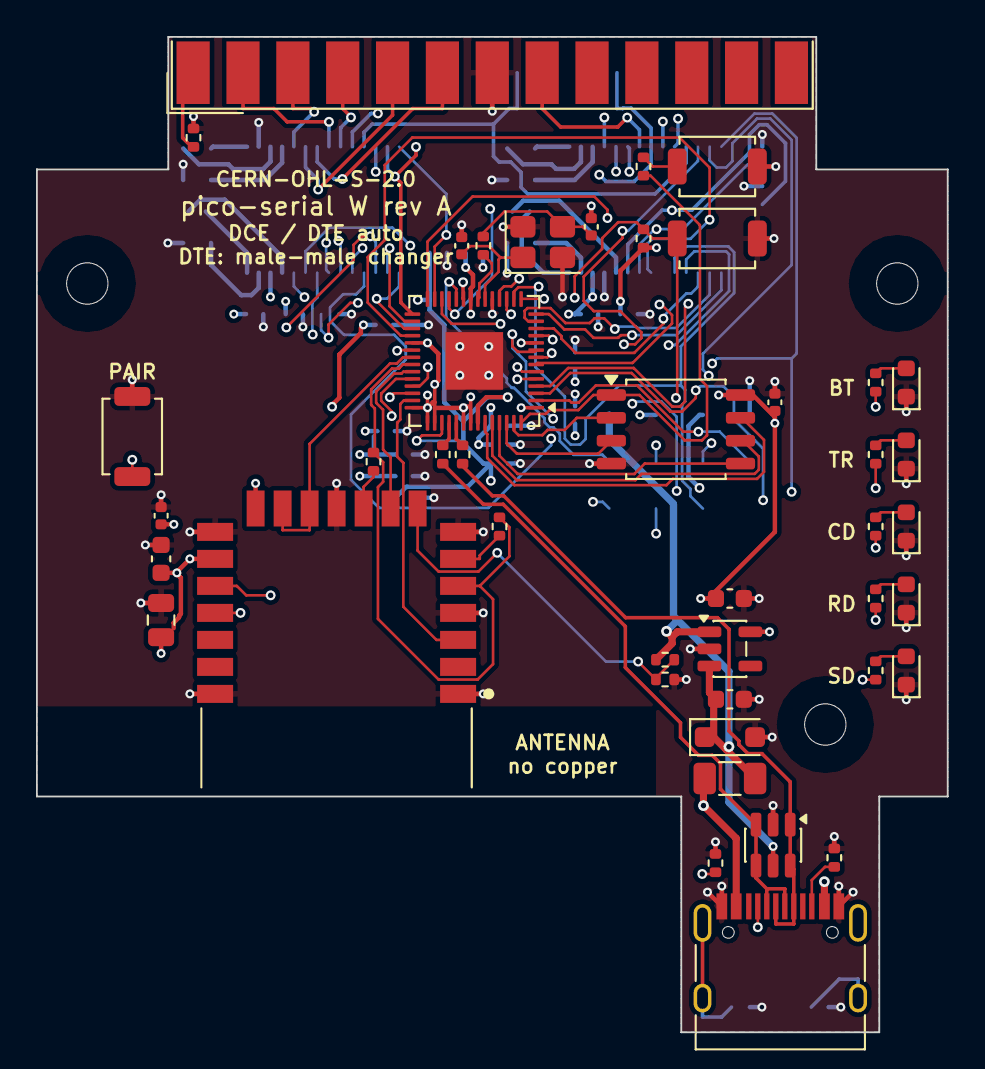
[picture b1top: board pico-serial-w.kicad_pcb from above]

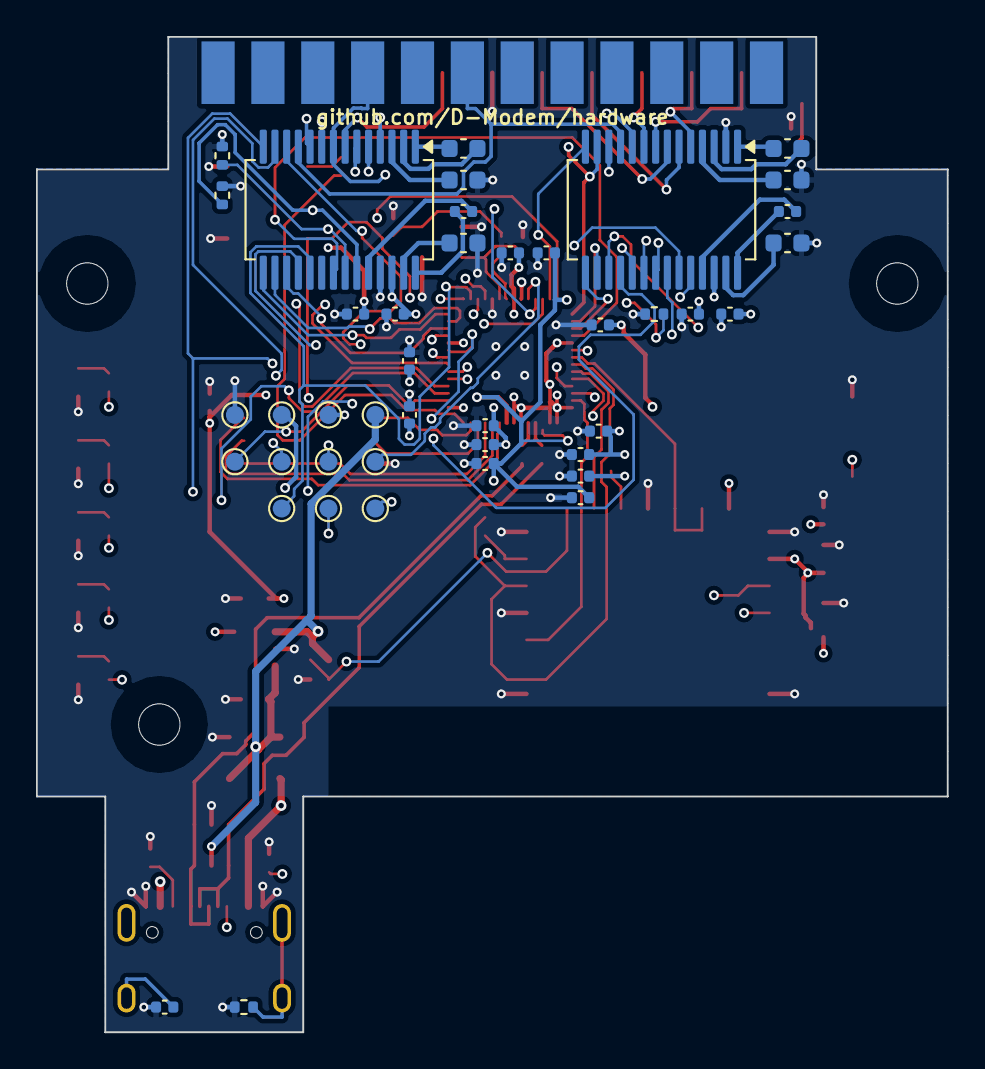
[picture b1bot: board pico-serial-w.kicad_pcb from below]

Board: 4 copper layers, 50.6 x 55.3 mm, 88 parts (42 on the bottom side), 86 nets.

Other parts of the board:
H1, H2, H3: M2 screw; MountingHole_M2

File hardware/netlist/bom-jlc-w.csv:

Comment,Designator,Footprint,LCSC Part #
4.7nF,"C1",C_0402_1005Metric,C1538
10uF,"C2,C3,C31",C_0603_1608Metric,C19702
100nF,"C4,C5,C6,C7,C8,C9,C10,C11,C14,C15,C18,C24,C30,C32",C_0402_1005Metric,C1525
1uF,"C12,C13,C23,C29",C_0402_1005Metric,C52923
15pF,"C16,C17",C_0402_1005Metric,C1548
220nF,"C19,C25",C_0402_1005Metric,C16772
1uF,"C20,C21,C22,C26,C27,C28",C_0603_1608Metric,C15849
22uF,"C33",C_0805_2012Metric,C45783
SMF5.0A,"D1",D_SOD-123F,C151296
LED_BT,"D2",LED_0603_1608Metric,C2286
LED_TR,"D3",LED_0603_1608Metric,C2286
LED_CD,"D4",LED_0603_1608Metric,C2286
LED_RD,"D5",LED_0603_1608Metric,C2286
LED_SD,"D6",LED_0603_1608Metric,C2286
0.5A,"F1",Fuse_1206_3216Metric,C163512
USB_C,"J1",USB_C_Receptacle_HRO_TYPE-C-31-M-12,C165948
5.1k,"R1,R2",R_0402_1005Metric,C25905
1M,"R3",R_0402_1005Metric,C26083
100k,"R4,R5,R12,R13,R14",R_0402_1005Metric,C25741
27R,"R6,R7",R_0402_1005Metric,C25100
1k,"R8,R9,R15,R16,R17,R18,R19",R_0402_1005Metric,C11702
10k,"R10,R21",R_0402_1005Metric,C25744
0R,"R11",R_0402_1005Metric,C17168
470R,"R20",R_0402_1005Metric,C25117
BOOTSEL,"SW1",SW_SPST_TS-1088-xR020,C720477
RESET,"SW2",SW_SPST_TS-1088-xR020,C720477
PAIR,"SW3",SW_SPST_TS-1088-xR020,C720477
RP2040,"U1",QFN-56-1EP_7x7mm_P0.4mm_EP3.2x3.2mm,C2040
W25Q128JVS,"U2",SOIC-8_5.3x5.3mm_P1.27mm,C97521
AP2112K-3.3,"U3",SOT-23-5,C51118
USBLC6-2SC6,"U4",SOT-23-6,C7519
SP3238EEA,"U5",SSOP-28_5.3x10.2mm_P0.65mm,C49669
MAX3243EIDBR,"U6",SSOP-28_5.3x10.2mm_P0.65mm,C353887
12MHz,"Y1",Crystal_SMD_3225-4Pin_3.2x2.5mm,C20625731

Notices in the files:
hardware/kicad/pico-serial-w.kicad_sch:
CERN-OHL-S-2.0 (or commercial licence from Neo-Desktop)
